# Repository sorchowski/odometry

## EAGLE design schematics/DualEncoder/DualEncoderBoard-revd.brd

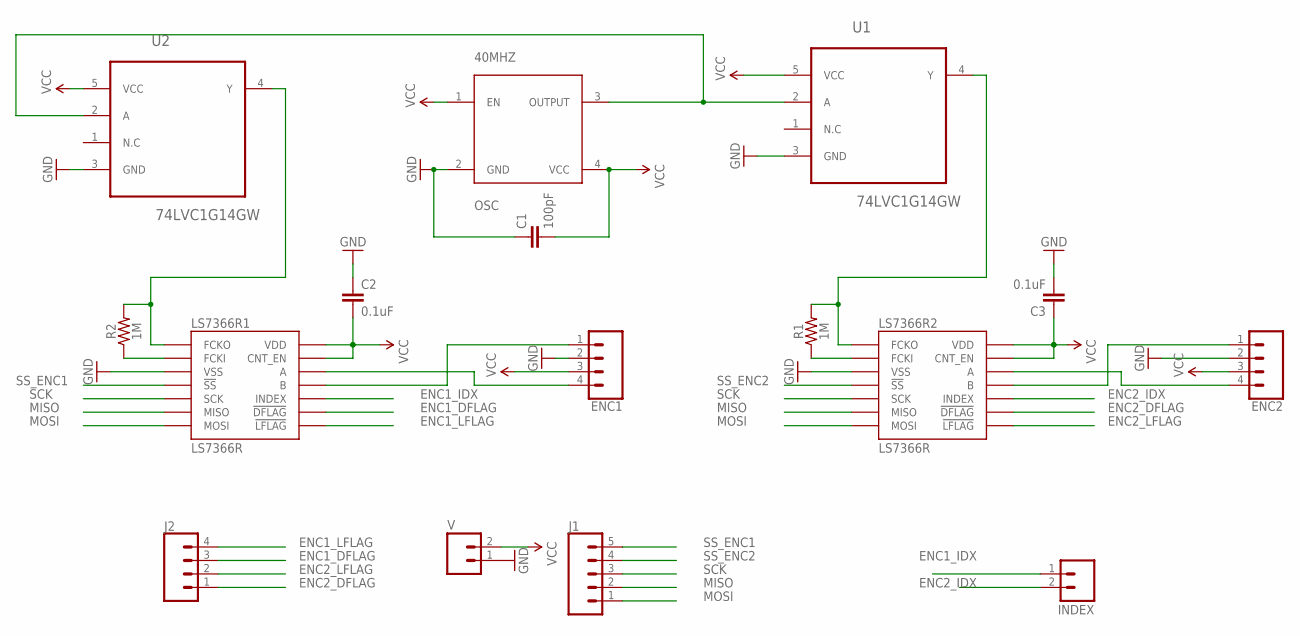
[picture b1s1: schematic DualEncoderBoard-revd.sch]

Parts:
40MHZ: OSC; CB3OSCILLATOR
C1: 100pF; 0603
C2, C3: 0.1uF; 0603
ENC1, ENC2: CONN_04; 1X04
INDEX: M02PTH; 1X02
J1: CONN_05; 1X05
J2: CONN_04; 1X04
LS7366R1, LS7366R2: LS7366R; SOIC14
R1, R2: 1M; 0603
U1, U2: 74LVC1G14GW; SOT65P210X110-5N
V: M02-JST-2MM-SMT; JST-2-SMD

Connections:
ENC1_DFLAG: J2.3, LS7366R1.9 (!DFLAG)
ENC1_IDX: INDEX.1, LS7366R1.10 (INDEX)
ENC1_LFLAG: J2.4, LS7366R1.8 (!LFLAG)
ENC2_DFLAG: J2.1, LS7366R2.9 (!DFLAG)
ENC2_IDX: INDEX.2, LS7366R2.10 (INDEX)
ENC2_LFLAG: J2.2, LS7366R2.8 (!LFLAG)
GND: 40MHZ.2 (GND), C1.1, C2.1, C3.2, ENC1.2, ENC2.2, LS7366R1.3 (VSS), LS7366R2.3 (VSS), U1.3 (GND), U2.3 (GND), V.1
MISO: J1.2, LS7366R1.6 (MISO), LS7366R2.6 (MISO)
MOSI: J1.1, LS7366R1.7 (MOSI), LS7366R2.7 (MOSI)
unnamed: ENC1.4, LS7366R1.12 (A)
unnamed: ENC1.1, LS7366R1.11 (B)
unnamed: ENC2.4, LS7366R2.12 (A)
unnamed: ENC2.1, LS7366R2.11 (B)
unnamed: LS7366R1.2 (FCKI), R2.1
unnamed: 40MHZ.3 (OUTPUT), U1.2 (A), U2.2 (A)
unnamed: LS7366R2.1 (FCKO), R1.2, U1.4 (Y)
unnamed: LS7366R2.2 (FCKI), R1.1
unnamed: LS7366R1.1 (FCKO), R2.2, U2.4 (Y)
SCK: J1.3, LS7366R1.5 (SCK), LS7366R2.5 (SCK)
SS_ENC1: J1.5, LS7366R1.4 (!SS)
SS_ENC2: J1.4, LS7366R2.4 (!SS)
VCC: 40MHZ.1 (EN), 40MHZ.4 (VCC), C1.2, C2.2, C3.1, ENC1.3, ENC2.3, LS7366R1.13 (CNT_EN), LS7366R1.14 (VDD), LS7366R2.13 (CNT_EN), LS7366R2.14 (VDD), U1.5 (VCC), U2.5 (VCC), V.2

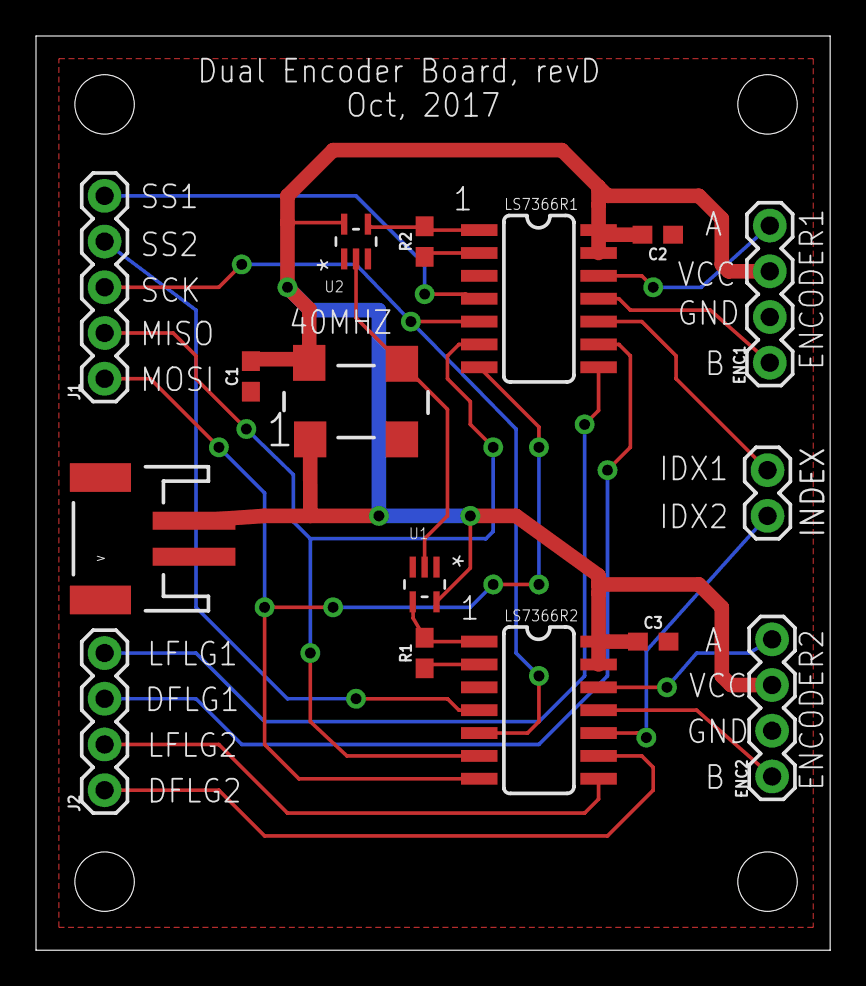
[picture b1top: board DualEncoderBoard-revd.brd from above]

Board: 2 copper layers, 44.1 x 50.8 mm, 20 parts (0 on the bottom side), 22 nets.

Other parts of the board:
U$1, U$2, U$3, U$4: STAND-OFF

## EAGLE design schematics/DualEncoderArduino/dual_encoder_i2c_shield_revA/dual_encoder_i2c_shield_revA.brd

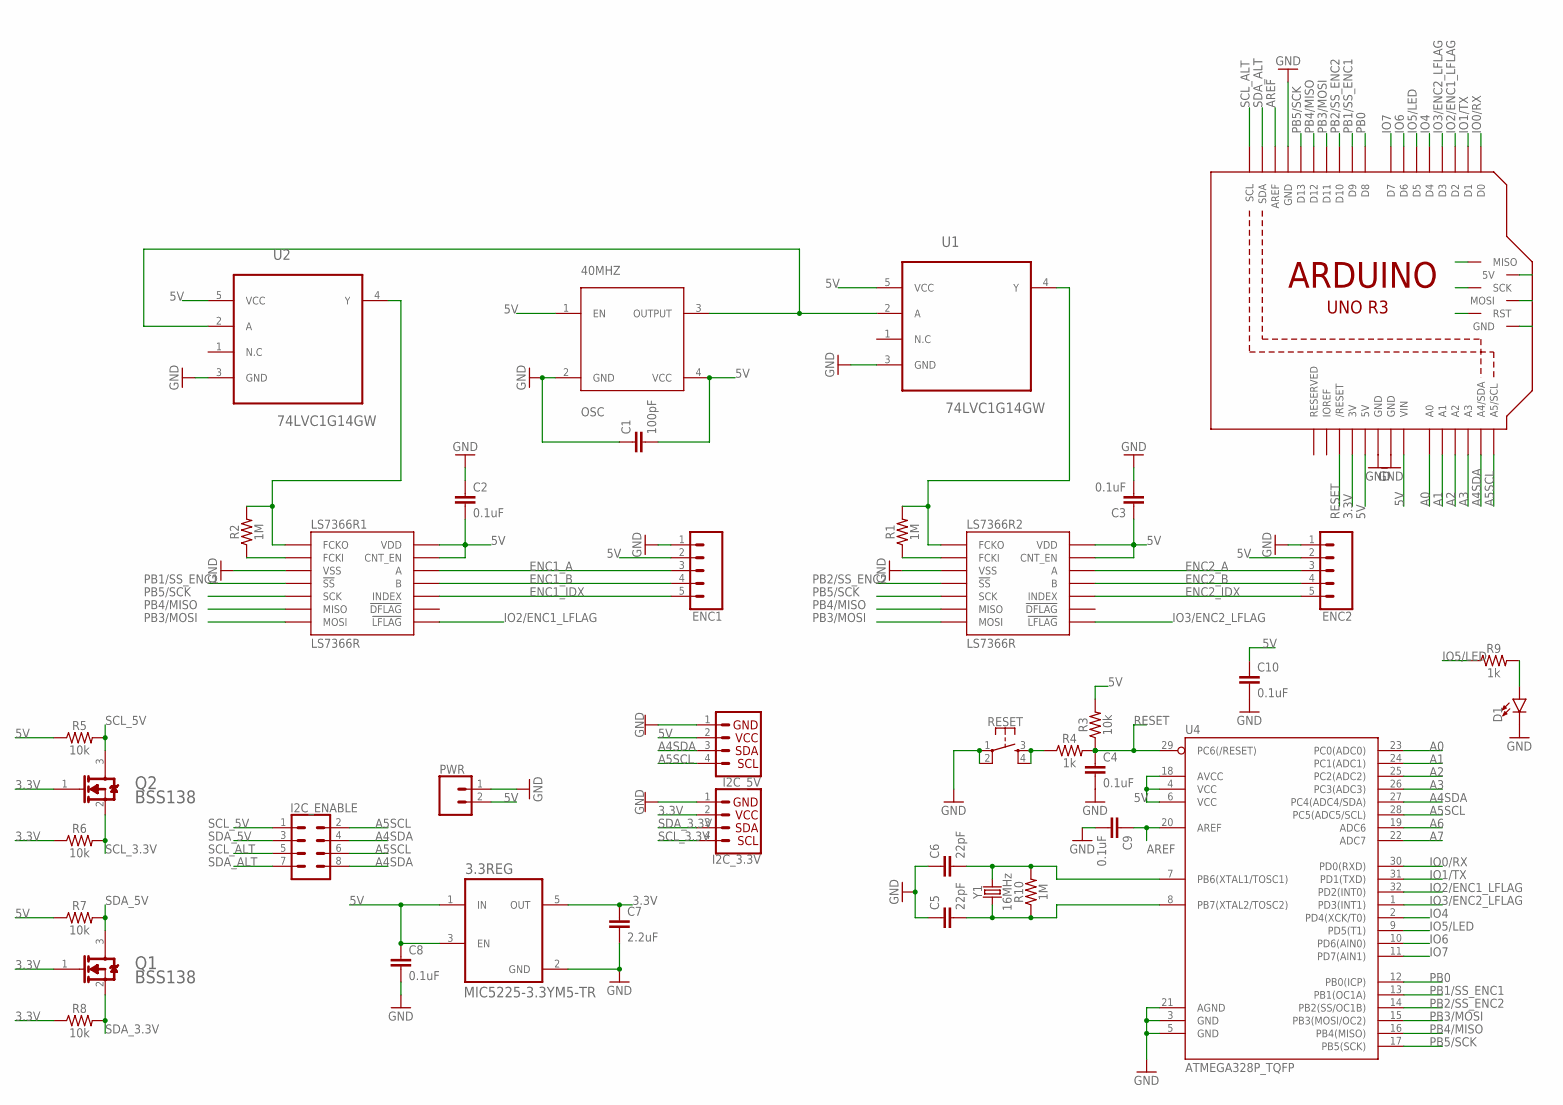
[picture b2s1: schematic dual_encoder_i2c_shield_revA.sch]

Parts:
3.3REG: MIC5225-3.3YM5-TR; SOT95P280X145-5N
40MHZ: OSC; CB3OSCILLATOR
C1: 100pF; 0603
C2, C3, C4, C8, C9, C10: 0.1uF; 0603
C5, C6: 22pF; 0603
C7: 2.2uF; 0603
D1: LED0603; LED-0603
ENC1, ENC2: CONN_05; 1X05
I2C_3.3V, I2C_5V: QWIIC_CONNECTORJS-1MM; JST04_1MM_RA
I2C_ENABLE: CONN_04X2; 2X4
LS7366R1, LS7366R2: LS7366R; SOIC14
M1: ARDUINO_R3_ICSP; ARDUINOR3_ICSP
PWR: CONN_02-JST-2MM-SMT; JST-2-SMD
Q1, Q2: ON_SEMI_BSS138ON_SEMI_BSS138_0_0; ON_SEMI_BSS138_0
R1, R2, R10: 1M; 0603
R3, R5, R6, R7, R8: 10k; 0603
R4, R9: 1k; 0603
RESET: MOMENTARY-SWITCH-SPST-2-SMD-5.2MM; TACTILE_SWITCH_SMD_5.2MM
U1, U2: 74LVC1G14GW; SOT65P210X110-5N
U4: ATMEGA328P_TQFP; TQFP32-08
Y1: 16MHz; HC49US

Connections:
3.3V: 3.3REG.5 (OUT), C7.1, I2C_3.3V.2, M1.3V, Q1.1 (G), Q2.1 (G), R6.1, R8.1
5V: 3.3REG.1 (IN), 3.3REG.3 (EN), 40MHZ.1 (EN), 40MHZ.4 (VCC), C1.2, C2.2, C3.1, C8.1, C10.1, ENC1.2, ENC2.2, I2C_5V.2, LS7366R1.13 (CNT_EN), LS7366R1.14 (VDD), LS7366R2.13 (CNT_EN), LS7366R2.14 (VDD), M1.5V, M1.5V_ICSP (5V), M1.VIN, PWR.2 (1), R3.2, R5.1, R7.1, U1.5 (VCC), U2.5 (VCC), U4.4 (VCC), U4.6 (VCC), U4.18 (AVCC)
A0: M1.A0, U4.23 (PC0(ADC0))
A1: M1.A1, U4.24 (PC1(ADC1))
A2: M1.A2, U4.25 (PC2(ADC2))
A3: M1.A3, U4.26 (PC3(ADC3))
A4SDA: I2C_5V.3, I2C_ENABLE.4, I2C_ENABLE.8, M1.A4 (A4/SDA), U4.27 (PC4(ADC4/SDA))
A5SCL: I2C_5V.4, I2C_ENABLE.2, I2C_ENABLE.6, M1.A5 (A5/SCL), U4.28 (PC5(ADC5/SCL))
A6: U4.19 (ADC6)
A7: U4.22 (ADC7)
AREF: C9.1, M1.AREF, U4.20 (AREF)
ENC1_A: ENC1.3, LS7366R1.12 (A)
ENC1_B: ENC1.4, LS7366R1.11 (B)
ENC1_IDX: ENC1.5, LS7366R1.10 (INDEX)
ENC2_A: ENC2.3, LS7366R2.12 (A)
ENC2_B: ENC2.4, LS7366R2.11 (B)
ENC2_IDX: ENC2.5, LS7366R2.10 (INDEX)
GND: 3.3REG.2 (GND), 40MHZ.2 (GND), C1.1, C2.1, C3.2, C4.2, C5.1, C6.1, C7.2, C8.2, C9.2, C10.2, D1.C, ENC1.1, ENC2.1, I2C_3.3V.1, I2C_5V.1, LS7366R1.3 (VSS), LS7366R2.3 (VSS), M1.GND, M1.GND@1 (GND), M1.GND@2 (GND), M1.GND@3 (GND), PWR.1 (2), RESET.1, RESET.2, U1.3 (GND), U2.3 (GND), U4.3 (GND), U4.5 (GND), U4.21 (AGND)
IO0/RX: M1.D0, U4.30 (PD0(RXD))
IO1/TX: M1.D1, U4.31 (PD1(TXD))
IO2/ENC1_LFLAG: LS7366R1.8 (!LFLAG), M1.D2, U4.32 (PD2(INT0))
IO3/ENC2_LFLAG: LS7366R2.8 (!LFLAG), M1.D3, U4.1 (PD3(INT1))
IO4: M1.D4, U4.2 (PD4(XCK/T0))
IO5/LED: M1.D5, R9.1, U4.9 (PD5(T1))
IO6: M1.D6, U4.10 (PD6(AIN0))
IO7: M1.D7, U4.11 (PD7(AIN1))
unnamed: R4.1, RESET.3, RESET.4
unnamed: D1.A, R9.2
unnamed: C6.2, R10.2, U4.7 (PB6(XTAL1/TOSC1)), Y1.2
unnamed: LS7366R1.2 (FCKI), R2.1
unnamed: 40MHZ.3 (OUTPUT), U1.2 (A), U2.2 (A)
unnamed: LS7366R2.1 (FCKO), R1.2, U1.4 (Y)
unnamed: LS7366R2.2 (FCKI), R1.1
unnamed: LS7366R1.1 (FCKO), R2.2, U2.4 (Y)
unnamed: C5.2, R10.1, U4.8 (PB7(XTAL2/TOSC2)), Y1.1
PB0: M1.D8, U4.12 (PB0(ICP))
PB1/SS_ENC1: LS7366R1.4 (!SS), M1.D9, U4.13 (PB1(OC1A))
PB2/SS_ENC2: LS7366R2.4 (!SS), M1.D10, U4.14 (PB2(SS/OC1B))
PB3/MOSI: LS7366R1.7 (MOSI), LS7366R2.7 (MOSI), M1.D11, M1.MOSI, U4.15 (PB3(MOSI/OC2))
PB4/MISO: LS7366R1.6 (MISO), LS7366R2.6 (MISO), M1.D12, M1.MISO, U4.16 (PB4(MISO))
PB5/SCK: LS7366R1.5 (SCK), LS7366R2.5 (SCK), M1.D13, M1.SCK, U4.17 (PB5(SCK))
RESET: C4.1, M1.RESET (/RESET), M1.RESET_ICSP (RST), R3.1, R4.2, U4.29 (PC6(/RESET))
SCL_3.3V: I2C_3.3V.4, Q2.2 (S), R6.2
SCL_5V: I2C_ENABLE.1, Q2.3 (D), R5.2
SCL_ALT: I2C_ENABLE.5, M1.SCL
SDA_3.3V: I2C_3.3V.3, Q1.2 (S), R8.2
SDA_5V: I2C_ENABLE.3, Q1.3 (D), R7.2
SDA_ALT: I2C_ENABLE.7, M1.SDA

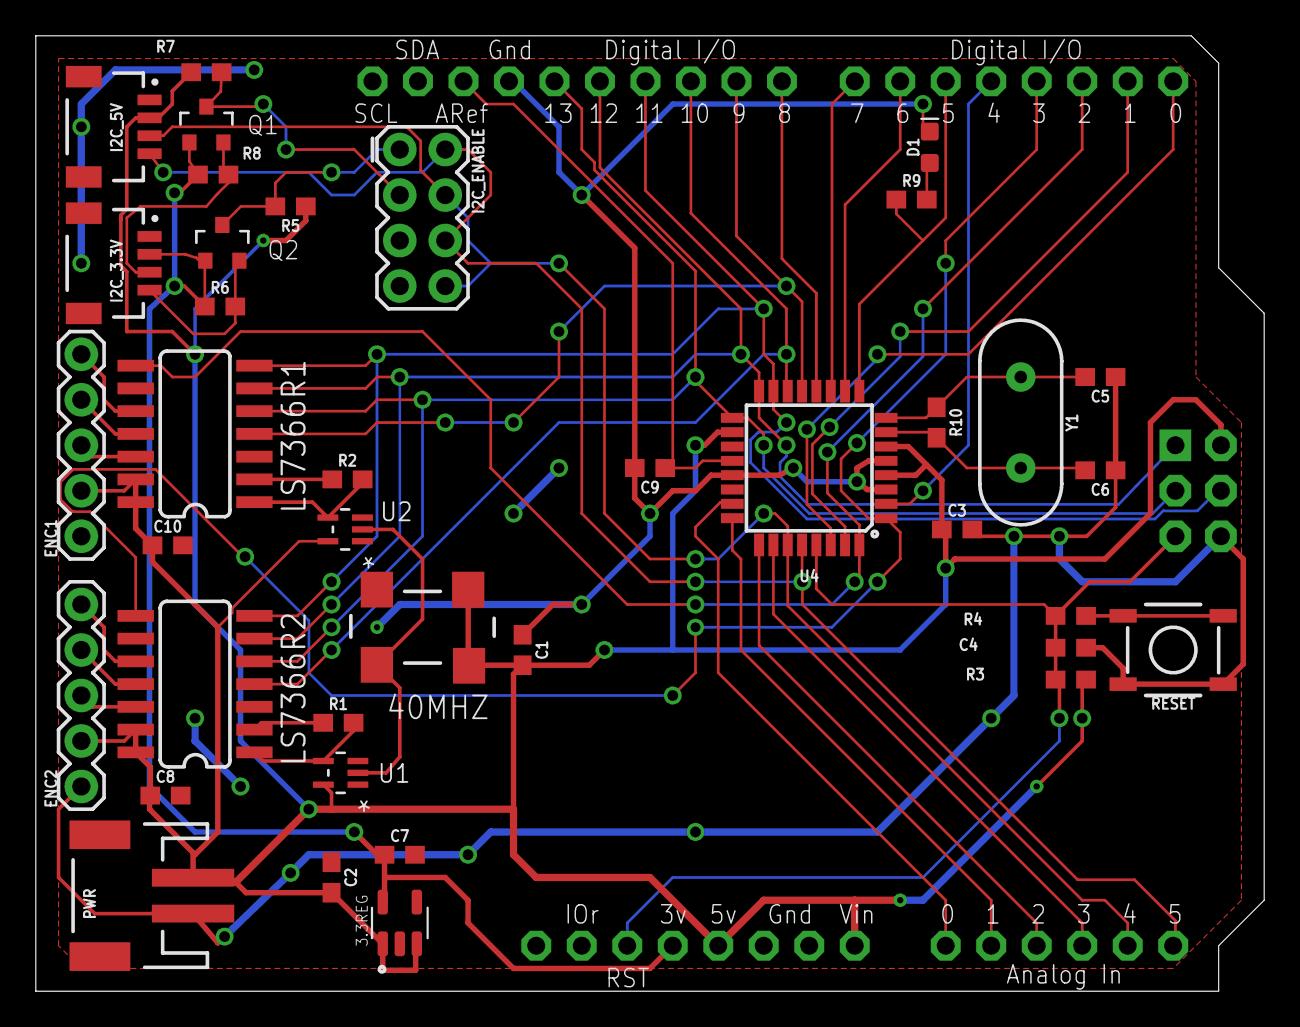
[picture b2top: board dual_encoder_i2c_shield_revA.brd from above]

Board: 2 copper layers, 68.6 x 53.3 mm, 39 parts (0 on the bottom side), 46 nets.

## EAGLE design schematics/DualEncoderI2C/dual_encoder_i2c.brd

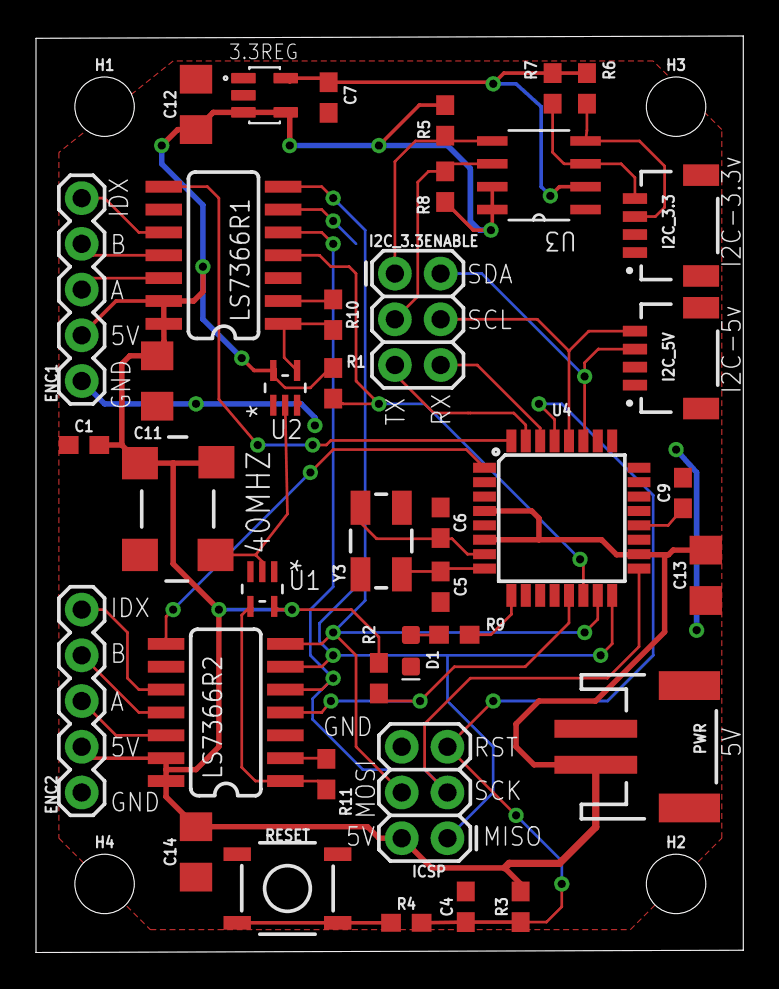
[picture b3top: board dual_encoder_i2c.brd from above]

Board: 2 copper layers, 39.3 x 50.9 mm, 43 parts (0 on the bottom side), 36 nets.

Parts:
3.3REG: SOT95P285X145-5N
40MHZ: OSC; CB3OSCILLATOR
C1: 100pF; 0603
C4, C9: 0.1uF; 0603
C5, C6: 22pF; 0603
C7: 2.2uF; 0603
C11, C12, C13, C14: 4.7uF; 1206
D1: LED; LED-0603
ENC1, ENC2: 1X05
H1, H2, H3, H4: STAND-OFF
I2C_3.3, I2C_5V: JST04_1MM_RA
I2C_3.3ENABLE: FEMALE 2x3; 2X3
ICSP: FEMALE 2x3; 2X3
LS7366R1, LS7366R2: LS7366R; SOIC14
PWR: JST-2-SMD
R1, R2, R4, R9: 1k; 0603
R3: 10k; 0603
R5, R6, R7, R8: 2.2k; 0603
R10, R11: 1M; 0603
RESET: TACTILE_SWITCH_SMD_5.2MM
U1, U2: 74LVC1G14GW; SOT65P210X110-5N
U3: PCA9306D,118; SOIC127P600X175-8N
U4: ATMEGA328P_TQFP; TQFP32-08
Y3: 16MHz; CRYSTAL-SMD-5X3.2-4PAD

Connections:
3.3V: 3.3REG.5, C7.1, R6.2, R7.1, U3.2
5V: 3.3REG.3, 3.3REG.4, 40MHZ.1, 40MHZ.4, C1.2, C11.1, C12.1, C13.2, C14.2, ENC1.2, ENC2.2, ICSP.2, LS7366R1.13, LS7366R1.14, LS7366R2.13, LS7366R2.14, PWR.2, R1.2, R2.2, R3.2, R5.2, R8.2, U1.5, U2.5, U3.7, U3.8, U4.4, U4.6, U4.18
ENC1_A: ENC1.3, LS7366R1.12
ENC1_B: ENC1.4, LS7366R1.11
ENC1_IDX: ENC1.5, LS7366R1.10
ENC1_LFLAG: LS7366R1.8, U4.32
ENC2_A: ENC2.3, LS7366R2.12
ENC2_B: ENC2.4, LS7366R2.11
ENC2_IDX: ENC2.5, LS7366R2.10
ENC2_LFLAG: LS7366R2.8, U4.1
GND: 3.3REG.2, 40MHZ.2, C1.1, C4.2, C5.1, C6.1, C7.2, C9.2, C11.2, C12.2, C13.1, C14.1, D1.C, ENC1.1, ENC2.1, I2C_3.3.1, I2C_5V.1, ICSP.6, LS7366R1.3, LS7366R2.3, PWR.1, RESET.1, RESET.2, U1.3, U2.3, U3.1, U4.3, U4.5, U4.21
LED: R9.1, U4.9
MISO: ICSP.1, LS7366R1.6, LS7366R2.6, U4.16
MOSI: ICSP.4, LS7366R1.7, LS7366R2.7, U4.15
unnamed: C9.1, U4.20
unnamed: R4.1, RESET.3, RESET.4
unnamed: D1.A, R9.2
unnamed: LS7366R2.2, R11.1
unnamed: LS7366R1.2, R10.1
unnamed: 40MHZ.3, U1.2, U2.2
unnamed: LS7366R2.1, R11.2, U1.4
unnamed: LS7366R1.1, R10.2, U2.4
unnamed: C6.2, U4.7, Y3.3
unnamed: C5.2, U4.8, Y3.1
RESET: C4.1, ICSP.5, R3.1, R4.2, U4.29
RX: I2C_3.3ENABLE.6, U4.30
SCK: ICSP.3, LS7366R1.5, LS7366R2.5, U4.17
SCL: I2C_3.3ENABLE.4, I2C_5V.4, U4.28
SCL_3.3V: I2C_3.3.4, R7.2, U3.3
SCL_5V: I2C_3.3ENABLE.3, R8.1, U3.6
SDA: I2C_3.3ENABLE.2, I2C_5V.3, U4.27
SDA_3.3V: I2C_3.3.3, R6.1, U3.4
SDA_5V: I2C_3.3ENABLE.1, R5.1, U3.5
SS_ENC1: LS7366R1.4, R1.1, U4.14
SS_ENC2: LS7366R2.4, R2.1, U4.13
TX: I2C_3.3ENABLE.5, U4.31

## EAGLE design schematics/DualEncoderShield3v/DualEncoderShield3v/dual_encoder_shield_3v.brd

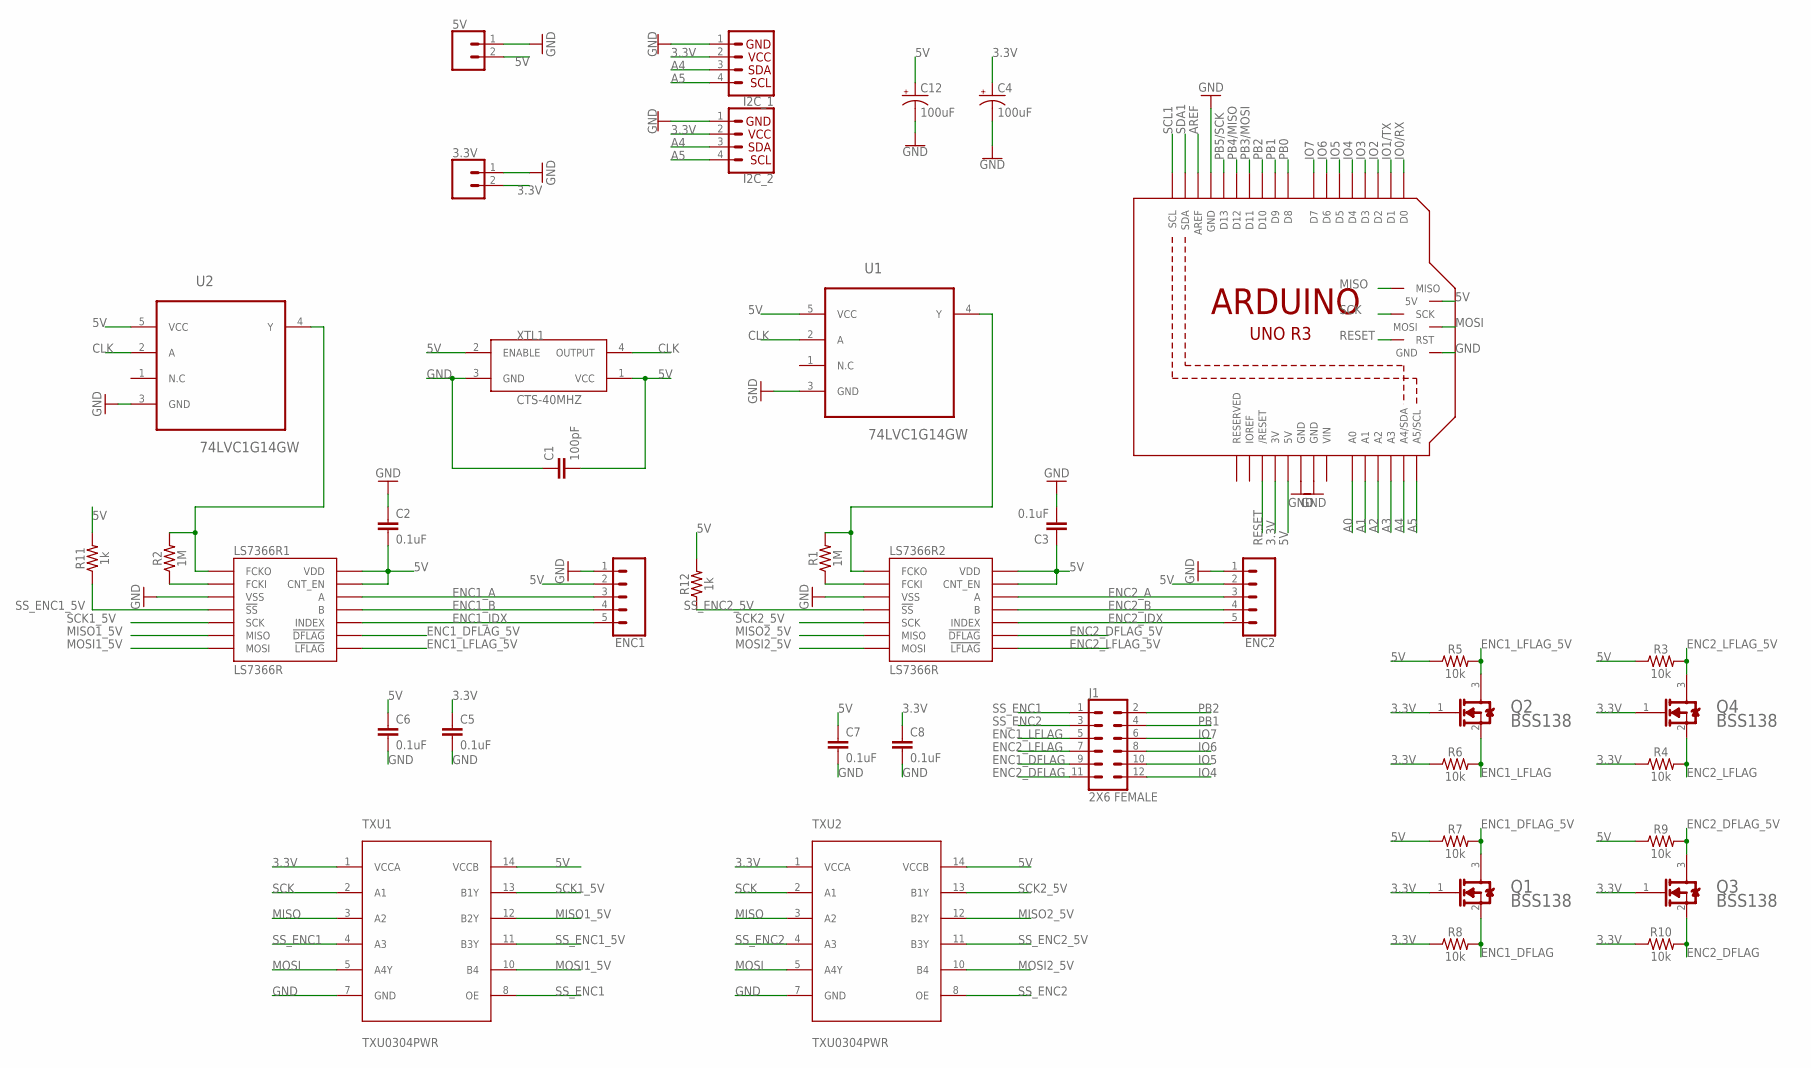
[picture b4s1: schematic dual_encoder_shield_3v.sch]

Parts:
3.3V, 5V: CONN_02-JST-2MM-SMT; JST-2-SMD
C1: 100pF; 0603
C2, C3, C5, C6, C7, C8: 0.1uF; 0603
C4, C12: 100uF; PANASONIC_D
ENC1, ENC2: CONN_05; 1X05
I2C_1, I2C_2: QWIIC_CONNECTORJS-1MM; JST04_1MM_RA
J1: 2X6 FEMALE; 2X6
LS7366R1, LS7366R2: LS7366R; SOIC14
M1: ARDUINO_R3_ICSP; ARDUINOR3_ICSP
Q1, Q2, Q3, Q4: ON_SEMI_BSS138ON_SEMI_BSS138_0_0; ON_SEMI_BSS138_0
R1, R2: 1M; 0603
R3, R4, R5, R6, R7, R8, R9, R10: 10k; 0603
R11, R12: 1k; 0603
TXU1, TXU2: TXU0304PWR; SOP65P640X95-14N
U1, U2: 74LVC1G14GW; SOT65P210X110-5N
XTL1: CTS-40MHZ; SOIC254P1016X440-4N

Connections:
3.3V: 3.3V.2 (1), C4.+, C5.1, C8.1, I2C_1.2, I2C_2.2, M1.3V, Q1.1 (G), Q2.1 (G), Q3.1 (G), Q4.1 (G), R4.1, R6.1, R8.1, R10.1, TXU1.1 (VCCA), TXU2.1 (VCCA)
5V: 5V.2 (1), C1.2, C2.2, C3.1, C6.1, C7.1, C12.+, ENC1.2, ENC2.2, LS7366R1.13 (CNT_EN), LS7366R1.14 (VDD), LS7366R2.13 (CNT_EN), LS7366R2.14 (VDD), M1.5V, M1.5V_ICSP (5V), R3.1, R5.1, R7.1, R9.1, R11.2, R12.2, TXU1.14 (VCCB), TXU2.14 (VCCB), U1.5 (VCC), U2.5 (VCC), XTL1.1 (VCC), XTL1.2 (ENABLE)
A0: M1.A0
A1: M1.A1
A2: M1.A2
A3: M1.A3
A4: I2C_1.3, I2C_2.3, M1.A4 (A4/SDA)
A5: I2C_1.4, I2C_2.4, M1.A5 (A5/SCL)
AREF: M1.AREF
CLK: U1.2 (A), U2.2 (A), XTL1.4 (OUTPUT)
ENC1_A: ENC1.3, LS7366R1.12 (A)
ENC1_B: ENC1.4, LS7366R1.11 (B)
ENC1_DFLAG: J1.9, Q1.2 (S), R8.2
ENC1_DFLAG_5V: LS7366R1.9 (!DFLAG), Q1.3 (D), R7.2
ENC1_IDX: ENC1.5, LS7366R1.10 (INDEX)
ENC1_LFLAG: J1.5, Q2.2 (S), R6.2
ENC1_LFLAG_5V: LS7366R1.8 (!LFLAG), Q2.3 (D), R5.2
ENC2_A: ENC2.3, LS7366R2.12 (A)
ENC2_B: ENC2.4, LS7366R2.11 (B)
ENC2_DFLAG: J1.11, Q3.2 (S), R10.2
ENC2_DFLAG_5V: LS7366R2.9 (!DFLAG), Q3.3 (D), R9.2
ENC2_IDX: ENC2.5, LS7366R2.10 (INDEX)
ENC2_LFLAG: J1.7, Q4.2 (S), R4.2
ENC2_LFLAG_5V: LS7366R2.8 (!LFLAG), Q4.3 (D), R3.2
GND: 3.3V.1 (2), 5V.1 (2), C1.1, C2.1, C3.2, C4.-, C5.2, C6.2, C7.2, C8.2, C12.-, ENC1.1, ENC2.1, I2C_1.1, I2C_2.1, LS7366R1.3 (VSS), LS7366R2.3 (VSS), M1.GND, M1.GND@1 (GND), M1.GND@2 (GND), M1.GND@3 (GND), TXU1.7 (GND), TXU2.7 (GND), U1.3 (GND), U2.3 (GND), XTL1.3 (GND)
IO0/RX: M1.D0
IO1/TX: M1.D1
IO2: M1.D2
IO3: M1.D3
IO4: J1.12, M1.D4
IO5: J1.10, M1.D5
IO6: J1.8, M1.D6
IO7: J1.6, M1.D7
MISO: M1.MISO, TXU1.3 (A2), TXU2.3 (A2)
MISO1_5V: LS7366R1.6 (MISO), TXU1.12 (B2Y)
MISO2_5V: LS7366R2.6 (MISO), TXU2.12 (B2Y)
MOSI: M1.MOSI, TXU1.5 (A4Y), TXU2.5 (A4Y)
MOSI1_5V: LS7366R1.7 (MOSI), TXU1.10 (B4)
MOSI2_5V: LS7366R2.7 (MOSI), TXU2.10 (B4)
unnamed: LS7366R1.2 (FCKI), R2.1
unnamed: LS7366R2.1 (FCKO), R1.2, U1.4 (Y)
unnamed: LS7366R2.2 (FCKI), R1.1
unnamed: LS7366R1.1 (FCKO), R2.2, U2.4 (Y)
PB0: M1.D8
PB1: J1.4, M1.D9
PB2: J1.2, M1.D10
PB3/MOSI: M1.D11
PB4/MISO: M1.D12
PB5/SCK: M1.D13
RESET: M1.RESET (/RESET), M1.RESET_ICSP (RST)
SCK: M1.SCK, TXU1.2 (A1), TXU2.2 (A1)
SCK1_5V: LS7366R1.5 (SCK), TXU1.13 (B1Y)
SCK2_5V: LS7366R2.5 (SCK), TXU2.13 (B1Y)
SCL1: M1.SCL
SDA1: M1.SDA
SS_ENC1: J1.1, TXU1.4 (A3), TXU1.8 (OE)
SS_ENC1_5V: LS7366R1.4 (!SS), R11.1, TXU1.11 (B3Y)
SS_ENC2: J1.3, TXU2.4 (A3), TXU2.8 (OE)
SS_ENC2_5V: LS7366R2.4 (!SS), R12.1, TXU2.11 (B3Y)
VIN: M1.VIN

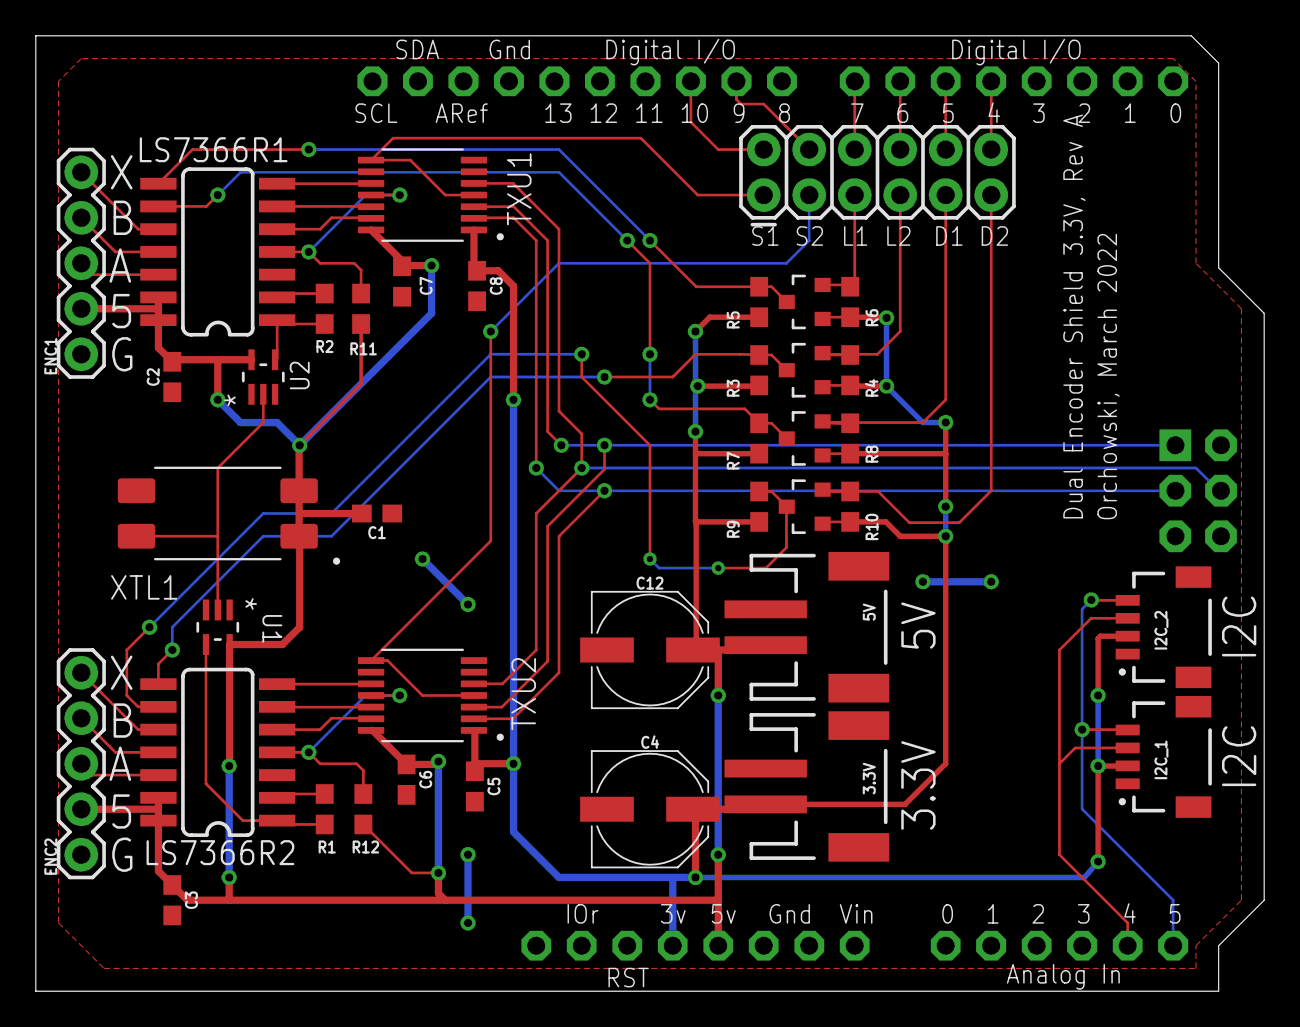
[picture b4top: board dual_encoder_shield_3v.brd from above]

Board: 2 copper layers, 68.6 x 53.3 mm, 40 parts (0 on the bottom side), 44 nets.

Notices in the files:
parts and their libraries:
SparkFun: Licensing: CC v3.0 Share-Alike You are welcome to use this library for commercial purposes.
SparkFun-Capacitors: Licensing: Creative Commons ShareAlike 4.0 International - https://creativecommons.org/licenses/by-sa/4.0
